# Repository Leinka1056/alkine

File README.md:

This is Alkine (currently only v1), my first attempt at a custom dev board. Alkine is meant to serve as a starting point for a variety of other projects i have/will think of.
(it is currently a PROTOTYPE, v2 will be actually good)

v1 front (render):

v1 back (render):

v1 is rather minimal, it includes the following features and/or properties:
- 3x qwiic connectors
- 5x gnd and 5x 3.3v (i never want to run out of these again)
- all module's pins accesible
- usb c 2.0 charging and data in (data from esp32 likely doesn't work, untested)
- rst/boot buttons
- 2x rgb led (second may not work, untested)
- dimensions (exc height) of a credit card
- fast charge toggle
- charge/pwr indicator leds and brakeout

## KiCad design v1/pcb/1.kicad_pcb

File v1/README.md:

This is v1 of Alkine, my first attempt at a custom dev board. Alkine is meant to serve as a starting point for a variety of other projects i have/will think of.
(it is currently a PROTOTYPE, v2 will be actually good)

Front (render):

Back (render):

v1 is rather minimal, it includes the following features and/or properties:
- 3x qwiic connectors
- 5x gnd and 5x 3.3v (i never want to run out of these again)
- all module's pins accesible
- usb c 2.0 charging and data in (data from esp32 likely doesn't work, untested)
- rst/boot buttons
- 2x rgb led (second may not work, untested)
- dimensions (exc height) of a credit card
- fast charge toggle
- charge/pwr indicator leds and brakeout

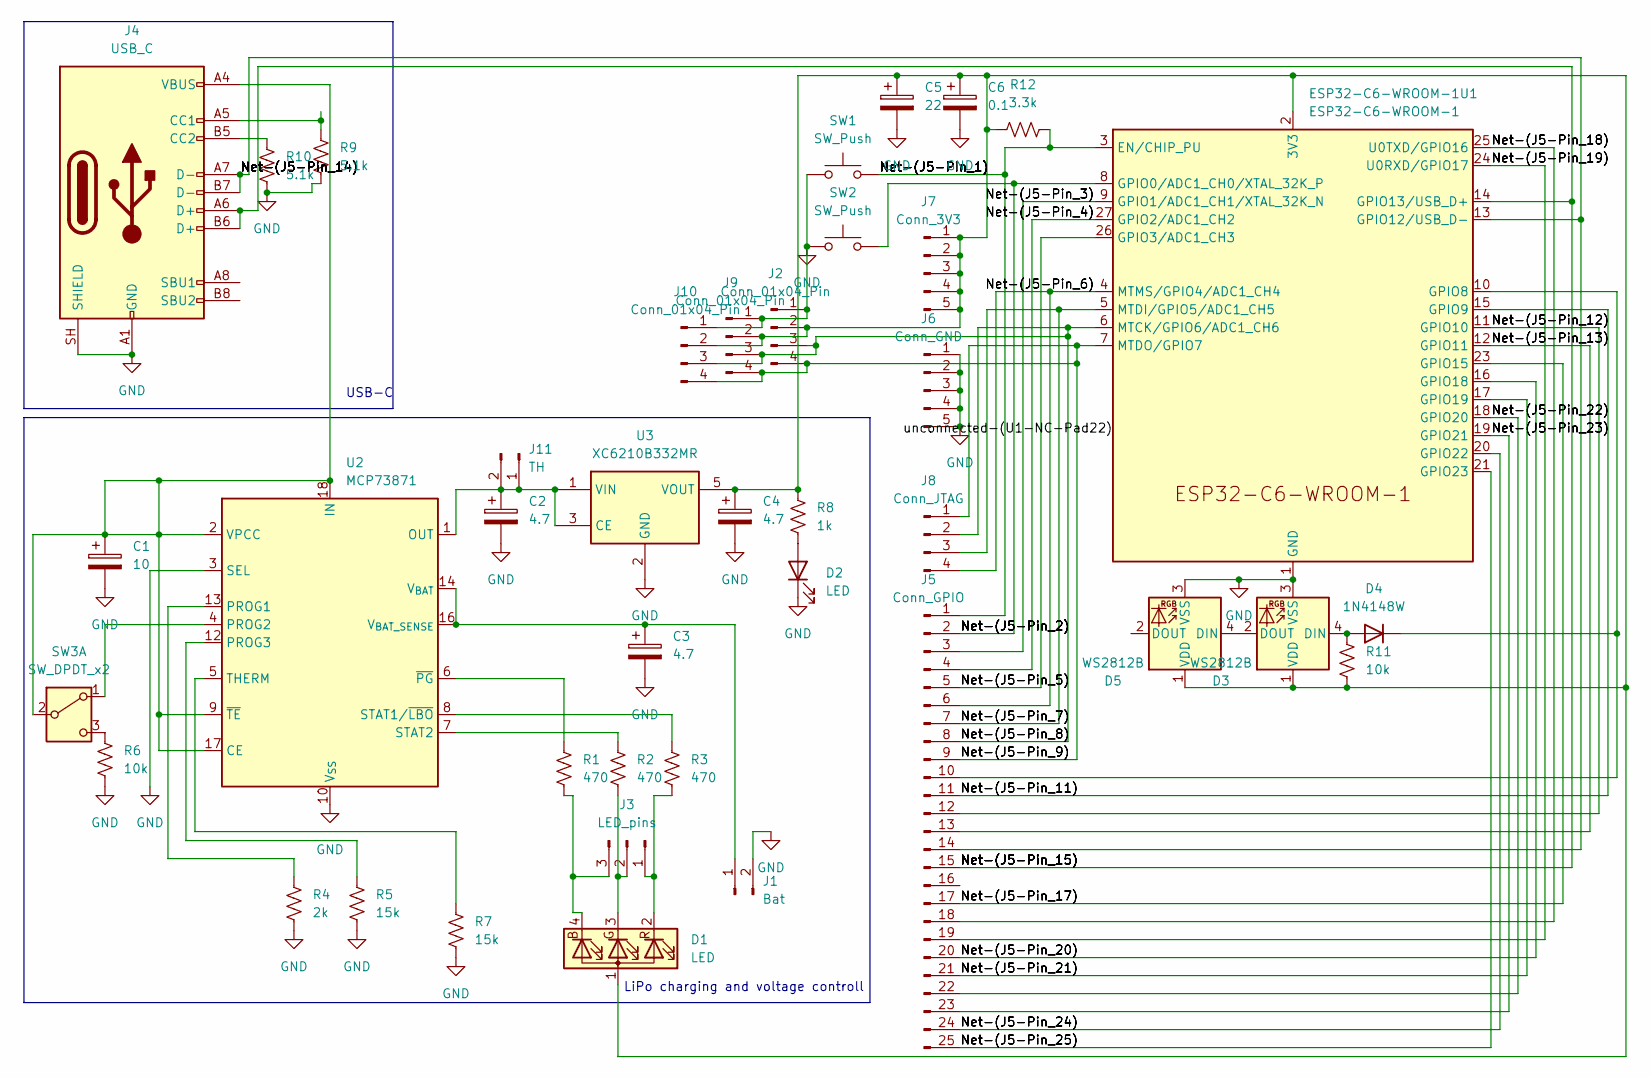
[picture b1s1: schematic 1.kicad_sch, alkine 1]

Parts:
C1: 10; CP_EIA-3216-10_Kemet-I_HandSolder
C2, C3, C4: 4.7; CP_EIA-3216-10_Kemet-I_HandSolder
C5: 22; CP_EIA-3216-10_Kemet-I_HandSolder
C6: 0.1; CP_EIA-3216-10_Kemet-I_HandSolder
D1: LED; LED_RGB_Wuerth-PLCC4_3.2x2.8mm_150141M173100
D2: LED; LED_1206_3216Metric_Pad1.42x1.75mm_HandSolder
D3, D5: WS2812B; LED_WS2812B_PLCC4_5.0x5.0mm_P3.2mm
D4: 1N4148W; D_SOD-123
ESP32-C6-WROOM-1U1: ESP32-C6-WROOM-1; ESP32-C6-WROOM-1U
J1: Bat; JST_PH_S2B-PH-K_1x02_P2.00mm_Horizontal
J2, J9, J10: Conn_01x04_Pin; JST_SH_SM04B-SRSS-TB_1x04-1MP_P1.00mm_Horizontal
J3: LED_pins; PinHeader_1x03_P1.00mm_Horizontal
J4: USB_C; USB_C_Receptacle_GCT_USB4085
J5: Conn_GPIO; PinHeader_1x25_P2.54mm_Horizontal
J6: Conn_GND; PinHeader_1x05_P2.54mm_Horizontal
J7: Conn_3V3; PinHeader_1x05_P2.54mm_Horizontal
J8: Conn_JTAG; PinHeader_1x04_P2.54mm_Horizontal
J11: TH; JST_PH_S2B-PH-K_1x02_P2.00mm_Horizontal
R1, R2, R3: 470; R_1206_3216Metric_Pad1.30x1.75mm_HandSolder
R4: 2k; R_1206_3216Metric_Pad1.30x1.75mm_HandSolder
R5, R7: 15k; R_1206_3216Metric_Pad1.30x1.75mm_HandSolder
R6, R11: 10k; R_1206_3216Metric_Pad1.30x1.75mm_HandSolder
R8: 1k; R_1206_3216Metric_Pad1.30x1.75mm_HandSolder
R9, R10: 5.1k; R_1206_3216Metric_Pad1.30x1.75mm_HandSolder
R12: 3.3k; R_1206_3216Metric_Pad1.30x1.75mm_HandSolder
SW1, SW2: SW_Push; SW_SPST_TS-1088-xR025
SW3: SW_DPDT_x2; SW_CK_JS202011AQN_DPDT_Angled
U2: MCP73871; QFN-20-1EP_4x4mm_P0.5mm_EP2.5x2.5mm
U3: XC6210B332MR; SOT-23-5_HandSoldering

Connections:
/Net-(J5-Pin_1): ESP32-C6-WROOM-1U1.3 (EN/CHIP_PU), J5.1, R12.2, SW1.2; also elsewhere on the board
/Net-(J5-Pin_2): ESP32-C6-WROOM-1U1.8 (GPIO0/ADC1_CH0/XTAL_32K_P), J5.2, SW2.2; also elsewhere on the board
/Net-(J5-Pin_3): ESP32-C6-WROOM-1U1.9 (GPIO1/ADC1_CH1/XTAL_32K_N), J5.3; also elsewhere on the board
/Net-(J5-Pin_4): ESP32-C6-WROOM-1U1.27 (GPIO2/ADC1_CH2), J5.4; also elsewhere on the board
/Net-(J5-Pin_5): ESP32-C6-WROOM-1U1.26 (GPIO3/ADC1_CH3), J5.5; also elsewhere on the board
/Net-(J5-Pin_6): ESP32-C6-WROOM-1U1.4 (MTMS/GPIO4/ADC1_CH4), J5.6, J8.4; also elsewhere on the board
/Net-(J5-Pin_7): ESP32-C6-WROOM-1U1.5 (MTDI/GPIO5/ADC1_CH5), J5.7, J8.3; also elsewhere on the board
/Net-(J5-Pin_8): ESP32-C6-WROOM-1U1.6 (MTCK/GPIO6/ADC1_CH6), J2.3, J5.8, J8.2, J9.3, J10.3; also elsewhere on the board
/Net-(J5-Pin_9): ESP32-C6-WROOM-1U1.7 (MTDO/GPIO7), J2.4, J5.9, J8.1, J9.4, J10.4; also elsewhere on the board
/Net-(J5-Pin_11): ESP32-C6-WROOM-1U1.15 (GPIO9), J5.11; also elsewhere on the board
/Net-(J5-Pin_12): ESP32-C6-WROOM-1U1.11 (GPIO10), J5.12; also elsewhere on the board
/Net-(J5-Pin_13): ESP32-C6-WROOM-1U1.12 (GPIO11), J5.13; also elsewhere on the board
/Net-(J5-Pin_14): ESP32-C6-WROOM-1U1.13 (GPIO12/USB_D-), J4.A7 (D-), J4.B7 (D-), J5.14; also elsewhere on the board
/Net-(J5-Pin_15): ESP32-C6-WROOM-1U1.14 (GPIO13/USB_D+), J4.A6 (D+), J4.B6 (D+), J5.15; also elsewhere on the board
/Net-(J5-Pin_17): ESP32-C6-WROOM-1U1.23 (GPIO15), J5.17; also elsewhere on the board
/Net-(J5-Pin_18): ESP32-C6-WROOM-1U1.25 (U0TXD/GPIO16), J5.18; also elsewhere on the board
/Net-(J5-Pin_19): ESP32-C6-WROOM-1U1.24 (U0RXD/GPIO17), J5.19; also elsewhere on the board
/Net-(J5-Pin_20): ESP32-C6-WROOM-1U1.16 (GPIO18), J5.20; also elsewhere on the board
/Net-(J5-Pin_21): ESP32-C6-WROOM-1U1.17 (GPIO19), J5.21; also elsewhere on the board
/Net-(J5-Pin_22): ESP32-C6-WROOM-1U1.18 (GPIO20), J5.22; also elsewhere on the board
/Net-(J5-Pin_23): ESP32-C6-WROOM-1U1.19 (GPIO21), J5.23; also elsewhere on the board
/Net-(J5-Pin_24): ESP32-C6-WROOM-1U1.20 (GPIO22), J5.24; also elsewhere on the board
/Net-(J5-Pin_25): ESP32-C6-WROOM-1U1.21 (GPIO23), J5.25; also elsewhere on the board
GND: C1.2, C2.2, C3.2, C4.2, C5.2, C6.2, D2.1 (K), D3.3 (VSS), D5.3 (VSS), ESP32-C6-WROOM-1U1.1 (GND), ESP32-C6-WROOM-1U1.28 (GND), ESP32-C6-WROOM-1U1.29 (GND), J1.2, J2.1, J4.A1 (GND), J4.A12 (GND), J4.B1 (GND), J4.B12 (GND), J4.SH (SHIELD), J6.1, J6.2, J6.3, J6.4, J6.5, J9.1, J10.1, R4.2, R5.2, R6.2, R7.2, R9.2, R10.2, SW1.1, SW2.1, U2.3 (SEL), U2.10 (V_{SS}), U2.11 (V_{SS}), U2.21 (V_{SS}), U3.2 (GND); also elsewhere on the board
unnamed 24: C4.1, C5.1, C6.1, D1.1 (A), D3.1 (VDD), D5.1 (VDD), ESP32-C6-WROOM-1U1.2 (3V3), J2.2, J7.1, J7.2, J7.3, J7.4, J7.5, J9.2, J10.2, R8.1, R11.2, R12.1, U3.5 (VOUT); also elsewhere on the board
unnamed: D1.4 (BK), J3.3, R1.2
unnamed: D1.3 (GK), J3.2, R2.2
unnamed: D1.2 (RK), J3.1, R3.2
unnamed: D2.2 (A), R8.2
unnamed: D3.4 (DIN), D4.2 (A), R11.1
unnamed: D3.2 (DOUT), D5.4 (DIN)
unnamed 31: D4.1 (K), ESP32-C6-WROOM-1U1.10 (GPIO8), J5.10; also elsewhere on the board
unnamed: C3.1, J1.1, U2.14 (V_{BAT}), U2.15 (V_{BAT}), U2.16 (V_{BAT_SENSE})
unnamed: J4.A5 (CC1), R9.1
unnamed: J4.B5 (CC2), R10.1
unnamed: C2.1, J11.1, J11.2, U2.1 (OUT), U2.20 (OUT), U3.1 (VIN), U3.3 (CE)
unnamed: SW3.1 (A), U2.4 (PROG2)
unnamed: C1.1, J4.A4 (VBUS), J4.A9 (VBUS), J4.B4 (VBUS), J4.B9 (VBUS), SW3.2 (B), U2.2 (VPCC), U2.9 (~TE), U2.17 (CE), U2.18 (IN), U2.19 (IN)
unnamed: R6.1, SW3.3 (C)
unnamed: R4.1, U2.13 (PROG1)
unnamed: R5.1, U2.12 (PROG3)
unnamed: R3.1, U2.8 (STAT1/~LBO)
unnamed: R2.1, U2.7 (STAT2)
unnamed: R7.1, U2.5 (THERM)
unnamed: R1.1, U2.6 (~PG)

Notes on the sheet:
LiPo charging and voltage controll
USB-C

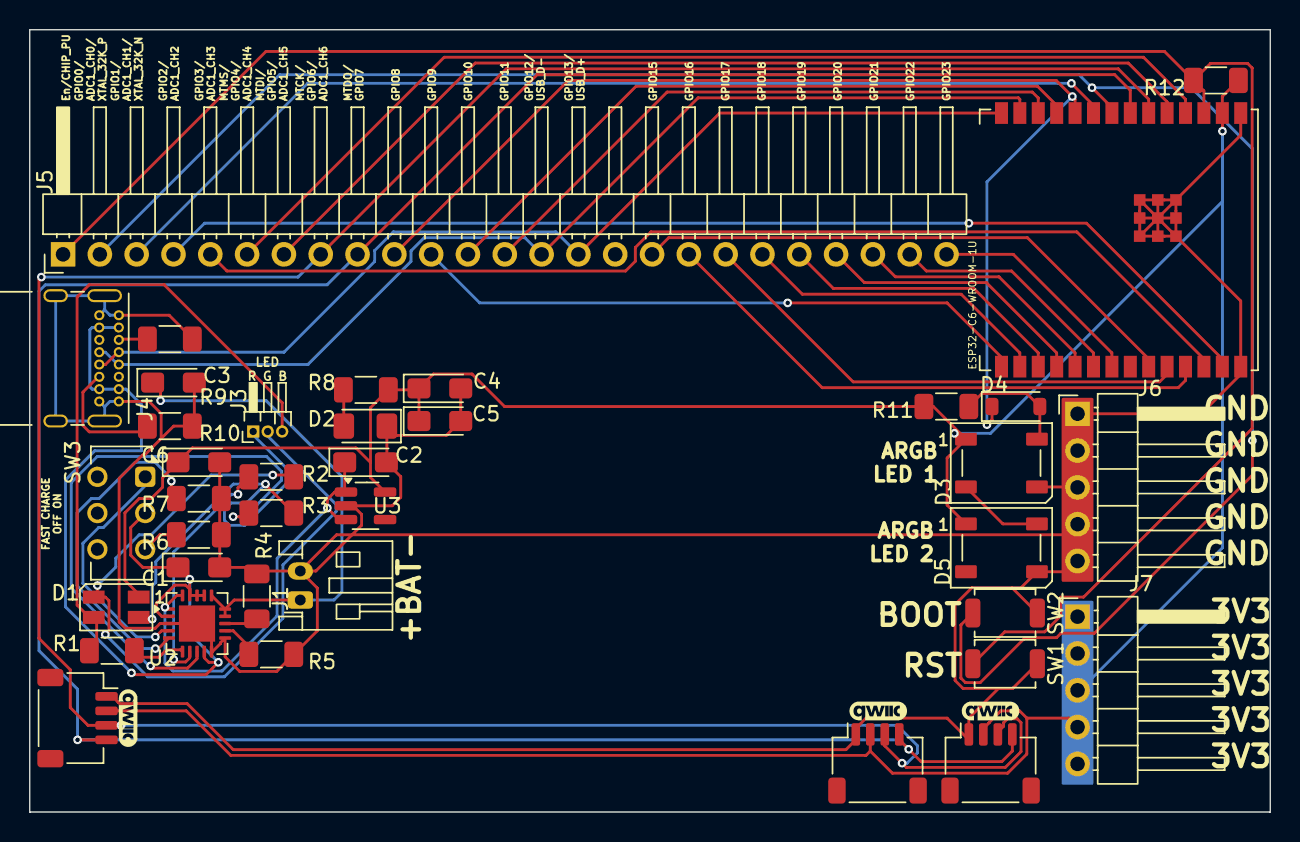
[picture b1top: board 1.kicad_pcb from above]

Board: 2 copper layers, 85.6 x 54.0 mm, 38 parts (0 on the bottom side), 45 nets.

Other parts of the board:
ESP32-C6-WROOM-1U: ESP32-C6-WROOM-1; ESP32-C6-WROOM-1U

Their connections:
/Net-(J5-Pin_1): ESP32-C6-WROOM-1U.3 (EN/CHIP_PU); also elsewhere on the board
/Net-(J5-Pin_2): ESP32-C6-WROOM-1U.8 (GPIO0/ADC1_CH0/XTAL_32K_P); also elsewhere on the board
/Net-(J5-Pin_3): ESP32-C6-WROOM-1U.9 (GPIO1/ADC1_CH1/XTAL_32K_N); also elsewhere on the board
/Net-(J5-Pin_4): ESP32-C6-WROOM-1U.27 (GPIO2/ADC1_CH2); also elsewhere on the board
/Net-(J5-Pin_5): ESP32-C6-WROOM-1U.26 (GPIO3/ADC1_CH3); also elsewhere on the board
/Net-(J5-Pin_6): ESP32-C6-WROOM-1U.4 (MTMS/GPIO4/ADC1_CH4); also elsewhere on the board
/Net-(J5-Pin_7): ESP32-C6-WROOM-1U.5 (MTDI/GPIO5/ADC1_CH5); also elsewhere on the board
/Net-(J5-Pin_8): ESP32-C6-WROOM-1U.6 (MTCK/GPIO6/ADC1_CH6); also elsewhere on the board
/Net-(J5-Pin_9): ESP32-C6-WROOM-1U.7 (MTDO/GPIO7); also elsewhere on the board
/Net-(J5-Pin_11): ESP32-C6-WROOM-1U.15 (GPIO9); also elsewhere on the board
/Net-(J5-Pin_12): ESP32-C6-WROOM-1U.11 (GPIO10); also elsewhere on the board
/Net-(J5-Pin_13): ESP32-C6-WROOM-1U.12 (GPIO11); also elsewhere on the board
/Net-(J5-Pin_14): ESP32-C6-WROOM-1U.13 (GPIO12/USB_D-); also elsewhere on the board
/Net-(J5-Pin_15): ESP32-C6-WROOM-1U.14 (GPIO13/USB_D+); also elsewhere on the board
/Net-(J5-Pin_17): ESP32-C6-WROOM-1U.23 (GPIO15); also elsewhere on the board
/Net-(J5-Pin_18): ESP32-C6-WROOM-1U.25 (U0TXD/GPIO16); also elsewhere on the board
/Net-(J5-Pin_19): ESP32-C6-WROOM-1U.24 (U0RXD/GPIO17); also elsewhere on the board
/Net-(J5-Pin_20): ESP32-C6-WROOM-1U.16 (GPIO18); also elsewhere on the board
/Net-(J5-Pin_21): ESP32-C6-WROOM-1U.17 (GPIO19); also elsewhere on the board
/Net-(J5-Pin_22): ESP32-C6-WROOM-1U.18 (GPIO20); also elsewhere on the board
/Net-(J5-Pin_23): ESP32-C6-WROOM-1U.19 (GPIO21); also elsewhere on the board
/Net-(J5-Pin_24): ESP32-C6-WROOM-1U.20 (GPIO22); also elsewhere on the board
/Net-(J5-Pin_25): ESP32-C6-WROOM-1U.21 (GPIO23); also elsewhere on the board
GND: ESP32-C6-WROOM-1U.1 (GND), ESP32-C6-WROOM-1U.28 (GND), ESP32-C6-WROOM-1U.29 (GND); also elsewhere on the board
unnamed 24: ESP32-C6-WROOM-1U.2 (3V3); also elsewhere on the board
unnamed 31: ESP32-C6-WROOM-1U.10 (GPIO8); also elsewhere on the board
